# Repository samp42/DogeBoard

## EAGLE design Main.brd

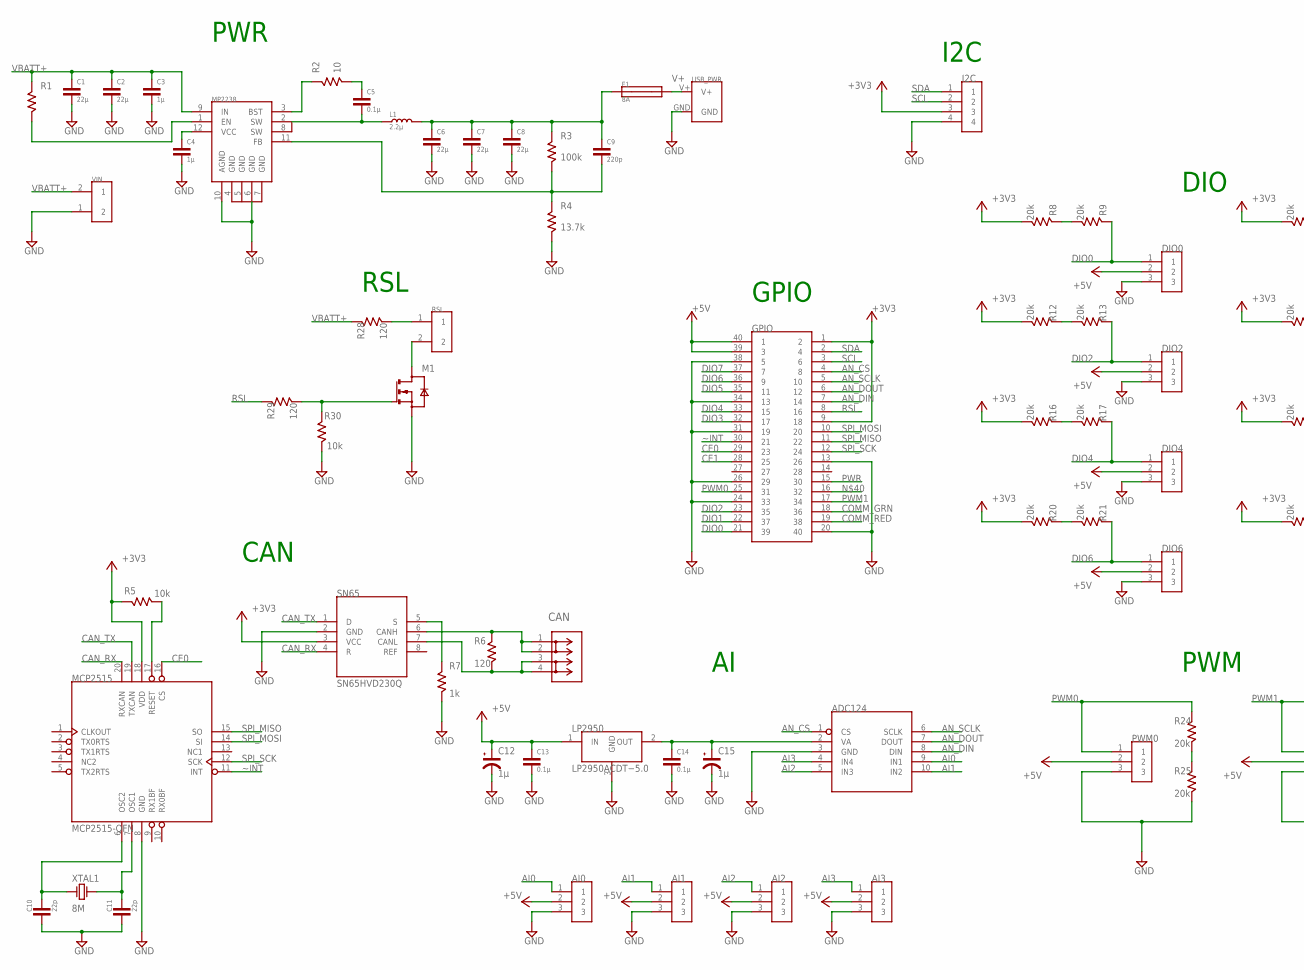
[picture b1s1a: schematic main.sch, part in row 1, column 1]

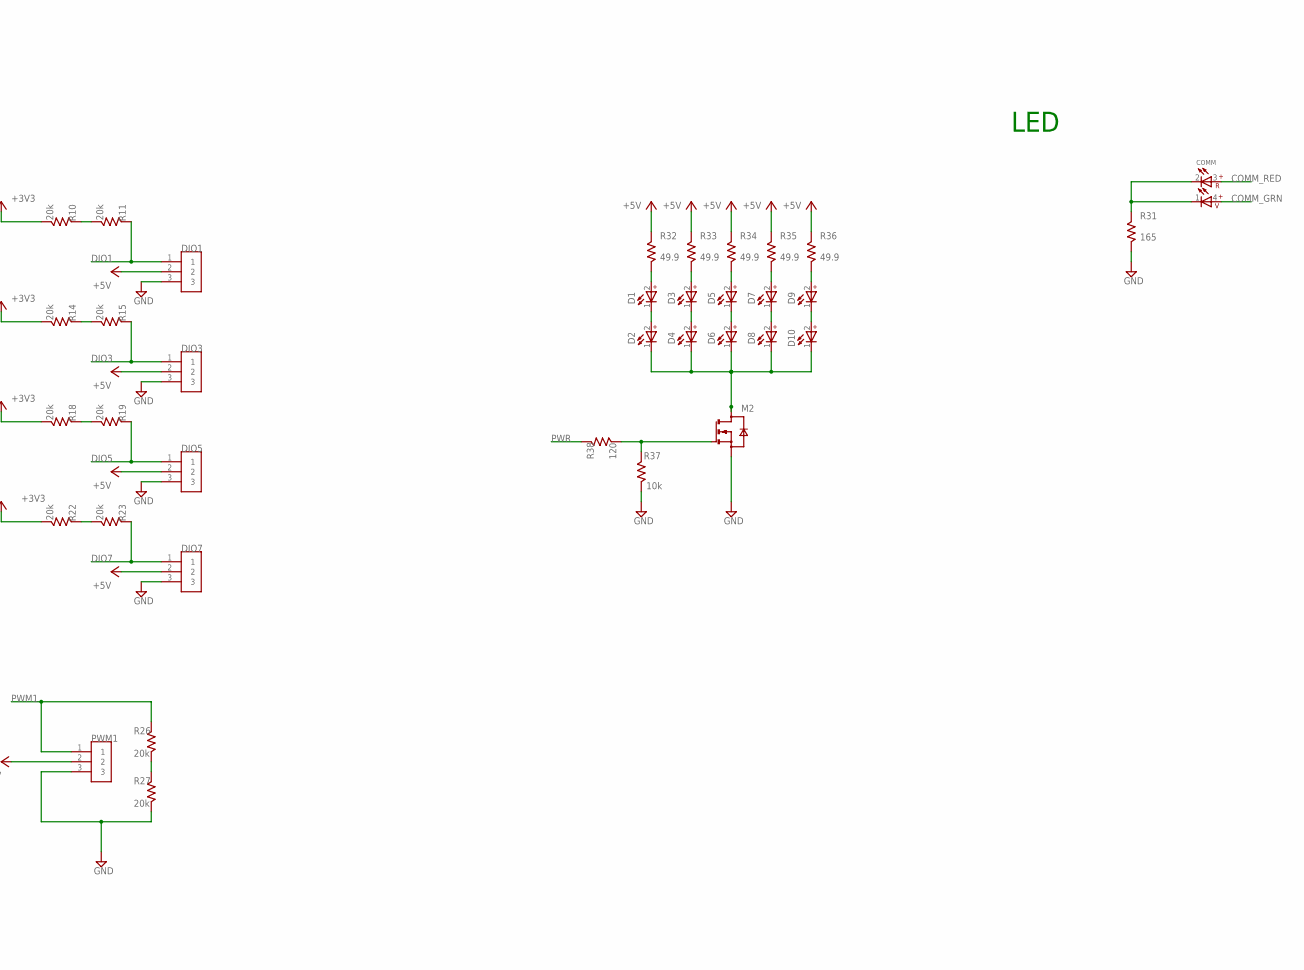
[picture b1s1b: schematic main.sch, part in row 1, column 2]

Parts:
ADC124: ADC124S051; SOP50P490X110-10N
AI0, AI1, AI2, AI3: 3X1_MALE_HEADER_PIN; HDRV3W64P254_1X3_762X254X838B
C1, C2, C6, C7, C8: 22µ; CAPC1912X140N
C3, C4: 1µ; CAPC1608X90N
C5, C13, C14: 0.1µ; CAPC1608X90N
C9: 220p; CAPC1608X90N
C10, C11: 22p; CAPC4020X56N
C12, C15: 1µ; CAPMP3216X180N
CAN: 1870640000; CONN_1870640000_WED
COMM: WL-SBCC_0603_150060RV75240; WL-SBCC_0603
D1, D2, D3, D4, D5, D6, D7, D8, D9, D10: WL-SMCD_0603_150060VS55040; WL-SMCD_0603
DIO0, DIO1, DIO2, DIO3, DIO4, DIO5, DIO6, DIO7: 3X1_MALE_HEADER_PIN; HDRV3W64P254_1X3_762X254X838B
F1: 8A; FUSC3216X117N
GPIO: 2X20_FEMALE_HEADER_PINV1; HDRVR40W64P254_2X20_5080X508X850B
I2C: 4X1_MALE_HEADER_PIN4X1_MALE_HEADER_PIN; HDRV4W64P254_1X4_1016X254X838B
L1: 2.2µ; INDM7166X300N
LP2950: LP2950ACDT−5.0; TO229P990X238-3N
M1, M2: MOSFET; SOT95P240X100-3N
MCP2515: MCP2515-QFN; QFN50P400X400X90-21T270N
MP2238: MP2238
PWM0, PWM1: 3X1_MALE_HEADER_PIN; HDRV3W64P254_1X3_762X254X838B
R1: 0603_RESISTOR; RESC1508X45N
R2: 10; RESC1508X45N
R3: 100k; RESC1508X45N
R4: 13.7k; RESC1508X45N
R5, R30, R37: 10k; RESC3116X55N
R6, R28, R29, R38: 120; RESC1508X45N
R7: 1k; RESC3116X55N
R8, R9, R10, R11, R12, R13, R14, R15, R16, R17, R18, R19, R20, R21, R22, R23, R24, R25, R26, R27: 20k; RESC2012X45N
R31: 165; RESC2012X45N
R32, R33, R34, R35, R36: 49.9; RESC1508X45N
RSL: 2X1_MALE_HEADER_PIN; HDRV2W64P254_1X2_508X254X838B
SN65: SN65HVD230Q; SOIC127P599X175-8N
USB_PWR: USB-C_POWER_PAD
VIN: CTF020V8
XTAL1: 8M; XTALRR488W60L1150T500H350B

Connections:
+3V3: GPIO.1 (2), GPIO.9 (18), I2C.3, MCP2515.18 (VDD), R5.1, R8.1, R10.1, R12.1, R14.1, R16.1, R18.1, R20.1, R22.1, SN65.3 (VCC)
+5V: AI0.2, AI1.2, AI2.2, AI3.2, C12.1, C13.1 (L1), DIO0.2, DIO1.2, DIO2.2, DIO3.2, DIO4.2, DIO5.2, DIO6.2, DIO7.2, GPIO.39 (3), GPIO.40 (1), LP2950.1 (IN), PWM0.2, PWM1.2, R32.2, R33.2, R34.2, R35.2, R36.2
AI0: ADC124.9 (IN1), AI0.1
AI1: ADC124.10 (IN2), AI1.1
AI2: ADC124.5 (IN3), AI2.1
AI3: ADC124.4 (IN4), AI3.1
AN_CS: ADC124.1 (CS), GPIO.4 (8)
AN_DIN: ADC124.8 (DIN), GPIO.7 (14)
AN_DOUT: ADC124.7 (DOUT), GPIO.6 (12)
AN_SCLK: ADC124.6 (SCLK), GPIO.5 (10)
CAN_RX: MCP2515.20 (RXCAN), SN65.4 (R)
CAN_TX: MCP2515.19 (TXCAN), SN65.1 (D)
CE0: GPIO.29 (23), MCP2515.16 (CS)
CE1: GPIO.28 (25)
COMM_GRN: COMM.4 (V+), GPIO.18 (36)
COMM_RED: COMM.3 (R+), GPIO.19 (38)
DIO0: DIO0.1, GPIO.21 (39), R9.2
DIO1: DIO1.1, GPIO.22 (37), R11.2
DIO2: DIO2.1, GPIO.23 (35), R13.2
DIO3: DIO3.1, GPIO.32 (17), R15.2
DIO4: DIO4.1, GPIO.33 (15), R17.2
DIO5: DIO5.1, GPIO.35 (11), R19.2
DIO6: DIO6.1, GPIO.36 (9), R21.2
DIO7: DIO7.1, GPIO.37 (7), R23.2
GND: ADC124.3 (GND), AI0.3, AI1.3, AI2.3, AI3.3, C1.2 (L2), C2.2 (L2), C3.2 (L2), C4.2 (L2), C6.2 (L2), C7.2 (L2), C8.2 (L2), C10.2 (L1), C11.2 (L1), C12.2, C13.2 (L2), C14.2 (L2), C15.2, DIO0.3, DIO1.3, DIO2.3, DIO3.3, DIO4.3, DIO5.3, DIO6.3, DIO7.3, GPIO.13 (26), GPIO.20 (40), GPIO.24 (33), GPIO.26 (29), GPIO.31 (19), GPIO.34 (13), GPIO.38 (5), I2C.4, LP2950.3 (GND), M1.2, M2.2, MCP2515.8 (GND), MP2238.6 (GND), MP2238.10 (AGND), PWM0.3, PWM1.3, R4.1, R7.2, R25.1, R27.1, R30.1, R31.1, R37.1, SN65.2 (GND), USB_PWR.GND, VIN.1 (2)
unnamed: M1.3, R29.1, R30.2
unnamed: C4.1 (L1), MP2238.12 (VCC)
unnamed: MP2238.3 (BST), R2.2
unnamed: MP2238.1 (EN), R1.1
unnamed: D1.1 (_), D2.2 (+)
unnamed: R8.2, R9.1
unnamed: D1.2 (+), R32.1
unnamed: D3.1 (_), D4.2 (+)
unnamed: D3.2 (+), R33.1
unnamed: D5.1 (_), D6.2 (+)
unnamed: R12.2, R13.1
unnamed: D5.2 (+), R34.1
unnamed: D7.1 (_), D8.2 (+)
unnamed: R16.2, R17.1
unnamed: R20.2, R21.1
unnamed: R10.2, R11.1
unnamed: R14.2, R15.1
unnamed: D7.2 (+), R35.1
unnamed: D9.1 (_), D10.2 (+)
unnamed: C10.1 (L2), MCP2515.6 (OSC2), XTAL1.1 (L1)
unnamed: R18.2, R19.1
unnamed: D9.2 (+), R36.1
unnamed: M2.3, R37.2, R38.1
unnamed: D2.1 (_), D4.1 (_), D6.1 (_), D8.1 (_), D10.1 (_), M2.1
unnamed: R22.2, R23.1
unnamed: R24.1, R25.2
unnamed: R26.1, R27.2
unnamed: CAN.1, CAN.2, R6.2, SN65.6 (CANH)
unnamed: CAN.3, CAN.4, R6.1, SN65.7 (CANL)
unnamed: R7.1, SN65.5 (S)
unnamed: ADC124.2 (VA), C14.1 (L1), C15.1, LP2950.2 (OUT)
unnamed: C11.1 (L2), MCP2515.7 (OSC1), XTAL1.2 (L2)
unnamed: C9.2 (L2), MP2238.11 (FB), R3.1, R4.2
unnamed: C6.1 (L1), C7.1 (L1), C8.1 (L1), C9.1 (L1), F1.1, L1.2, R3.2
unnamed: MCP2515.17 (RESET), R5.2
unnamed: C5.2 (L2), L1.1, MP2238.2 (SW)
unnamed: C5.1 (L1), R2.1
unnamed: R28.1, RSL.1
unnamed: M1.1, RSL.2
unnamed: COMM.1 (V-), COMM.2 (R-), R31.2
PWM0: GPIO.25 (31), PWM0.1, R24.2
PWM1: GPIO.17 (34), PWM1.1, R26.2
PWR: GPIO.15 (30), R38.2
RSL: GPIO.8 (16), R29.2
SCL: GPIO.3 (6), I2C.2
SDA: GPIO.2 (4), I2C.1
SPI_MISO: GPIO.11 (22), MCP2515.15 (SO)
SPI_MOSI: GPIO.10 (20), MCP2515.14 (SI)
SPI_SCK: GPIO.12 (24), MCP2515.12 (SCK)
V+: F1.2, USB_PWR.V+
VBATT+: C1.1 (L1), C2.1 (L1), C3.1 (L1), MP2238.9 (IN), R1.2, R28.2, VIN.2 (1)
~INT: GPIO.30 (21), MCP2515.11 (INT)

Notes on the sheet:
DIO
I2C
GPIO
PWM
CAN
PWR
RSL
LED

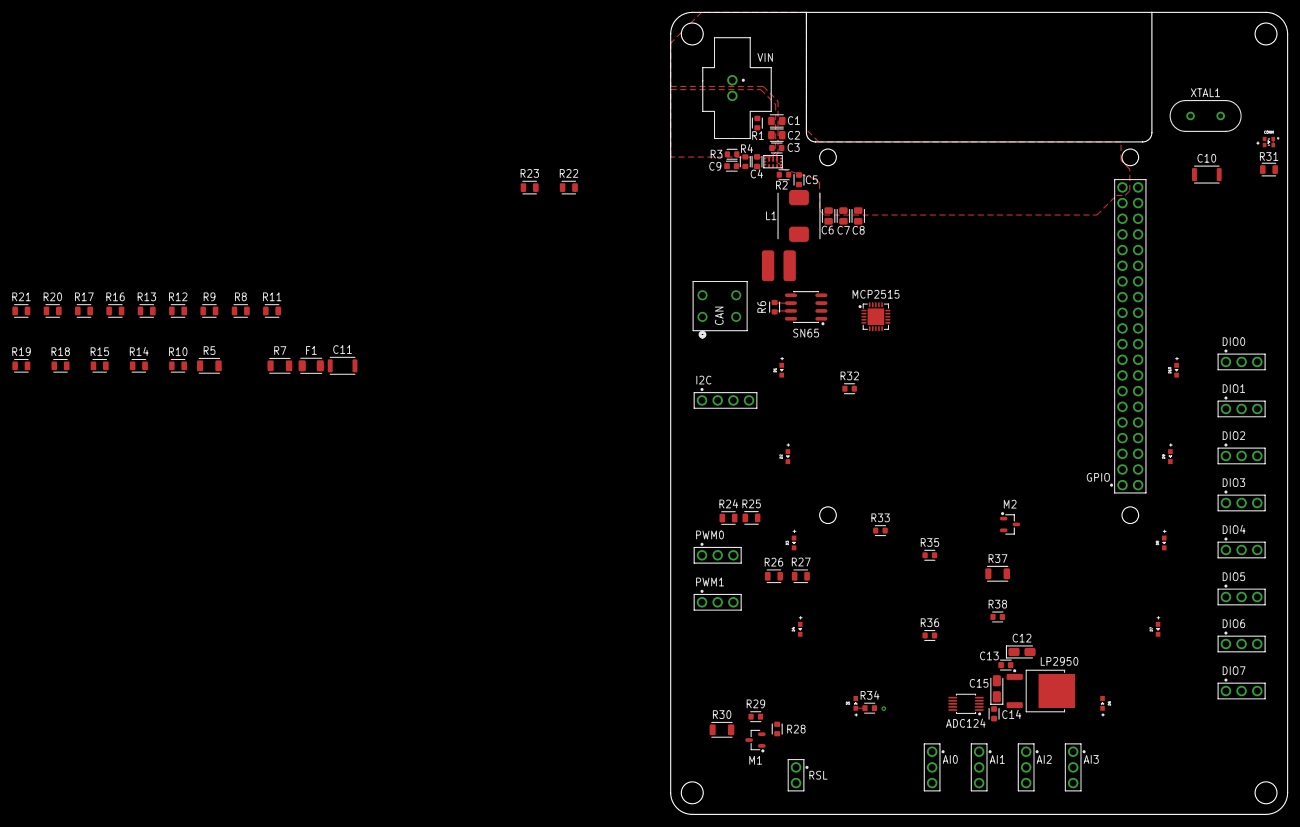
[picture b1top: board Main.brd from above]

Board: 4 copper layers, 100.0 x 130.0 mm, 94 parts (0 on the bottom side), 76 nets.

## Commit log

2021-04-05 datasheets
2021-04-05 inital buck converter design
2021-04-22 reviewed buck converter
2021-05-04 slow progress
2021-05-07 specs
2021-05-10 modules advancement
2021-05-12 peripherals advancement
2021-05-18 work on crystal
2021-05-20 added 0402 capacitor
2021-05-21 can interface and data sheets
2021-05-21 pi can hat doc
2021-05-23 adc power supply
2021-05-25 adc and pwr
2021-05-26 power module
2021-05-30 finished schematics parts
2021-05-31 board layout
2021-06-01 power block layout
2021-06-03 dope pwr led system
2021-06-04 dope led system led placement
2021-06-11 board layout and planes
2021-07-07 pew pew

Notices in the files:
parts and their libraries:
COPYRIGHT: Copyright (C) 2018 Accelerated Designs. All rights reserved
